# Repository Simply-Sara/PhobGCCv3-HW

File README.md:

# PhobGCCv3-HW
Seperate repository for the hardware used in the PhobGCC v3.0

The PhobGCC v3.0 board is licensed under CERN Open Hardware Licence Version 2 - Strongly Reciprocal.
This means that any changes made to the board should be made public and CHANGES.txt be updated to reflect said changes.

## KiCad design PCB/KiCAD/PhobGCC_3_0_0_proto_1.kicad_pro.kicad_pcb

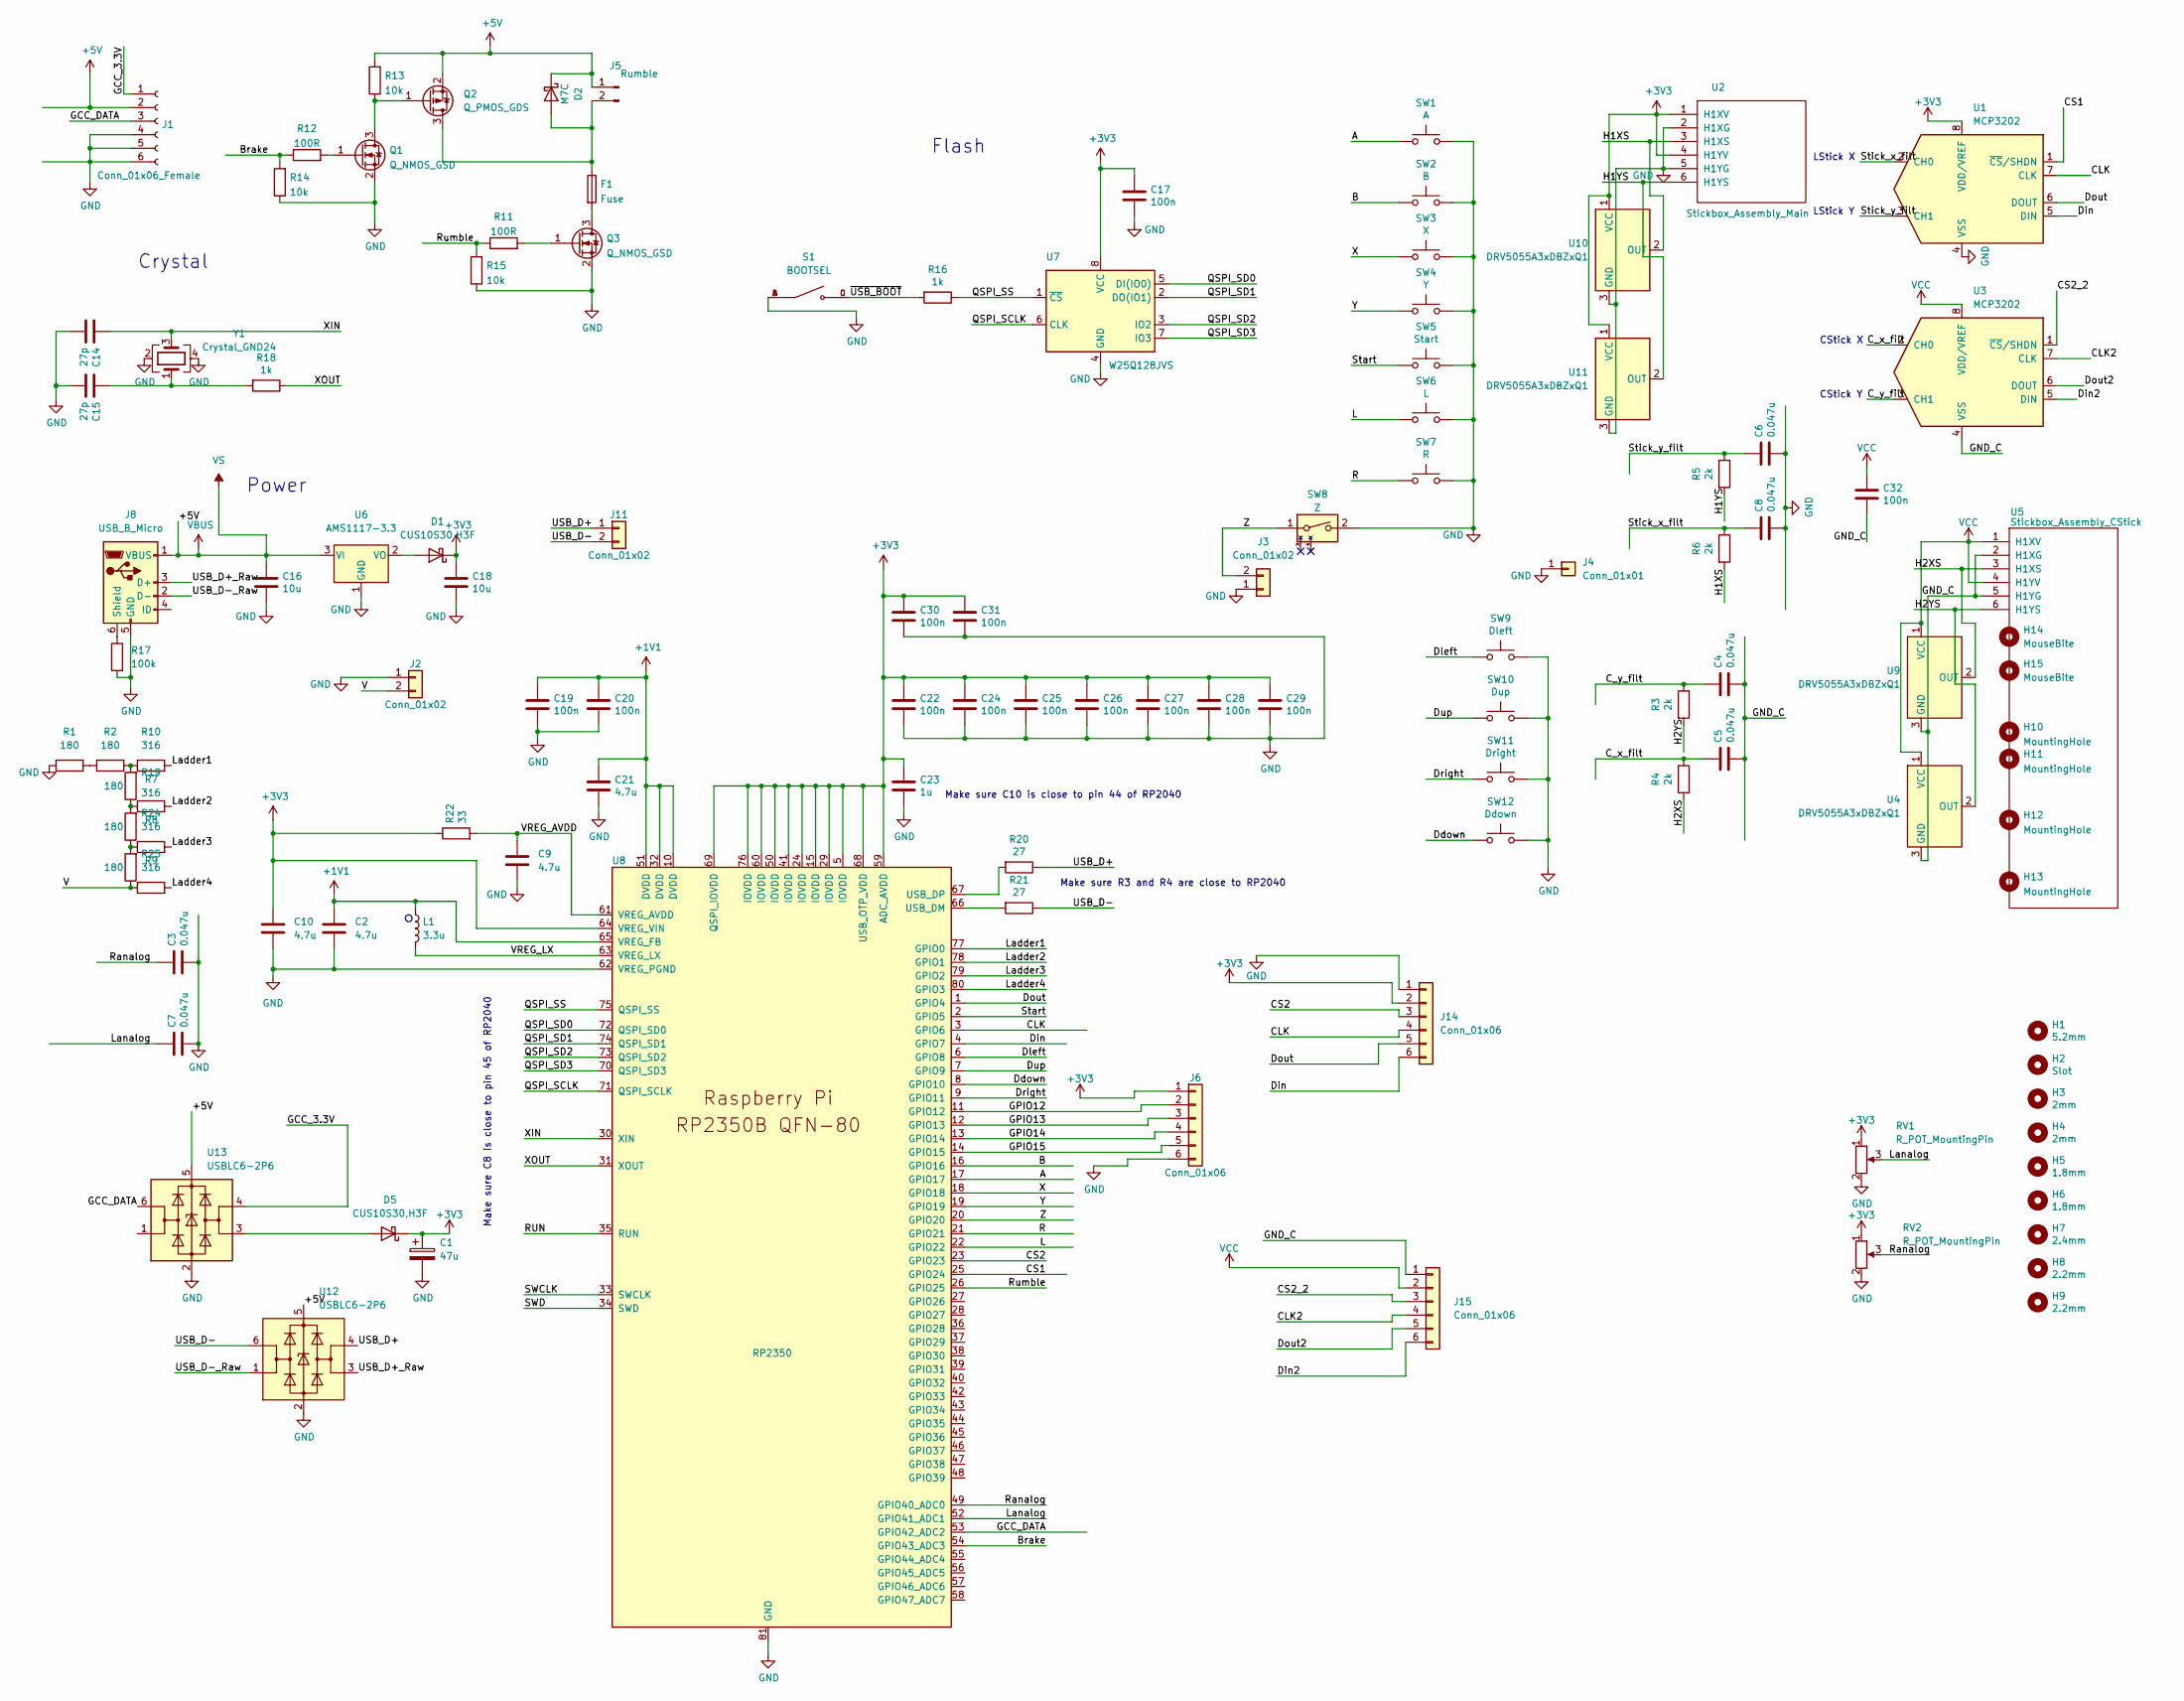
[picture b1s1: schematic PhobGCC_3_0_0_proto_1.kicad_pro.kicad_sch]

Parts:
C1: 47u; CP_EIA-3528-12_Kemet-T_Pad1.50x2.35mm_HandSolder; LCSC C136751
C2, C10: 4.7u; C_0402_1005Metric_small_pads
C3, C4, C5, C6, C7, C8: 0.047u; C_0603_HandSoldering; LCSC C1622
C9: 4.7u; C_0402_1005Metric
C14, C15: 27p; C_0402_1005Metric; LCSC C1557
C16, C18: 10u; C_0805_2012Metric; LCSC C15850
C17, C19, C20, C22, C24, C25, C26, C27, C28, C29, C30, C31, C32: 100n; C_0402_1005Metric; LCSC C1525
C21: 4.7u; C_0402_1005Metric; LCSC C52923
C23: 1u; C_0402_1005Metric; LCSC C52923
D1, D5: CUS10S30,H3F; D_SOD-323; LCSC C146335
D2: M7C; D_SOD-123; LCSC C8598
F1: Fuse; Fuse_1206_3216Metric; LCSC C69680
H1: 5.2mm; MountingHole_5.2mm
H2: Slot
H3, H4: 2mm; MountingHole_2.0mm
H5, H6: 1.8mm; MountingHole_1.8mm
H7: 2.4mm; MountingHole_2.4mm
H8, H9: 2.2mm; MountingHole_2.2mm
H10: MountingHole; MountingHole_1.8mm
H11: MountingHole; MountingHole_5.2mm
H12, H13: MountingHole; MountingHole_2.0mm
H14: MouseBite; breakaway-mousebites-double-v2-small
H15: MouseBite; breakaway-mousebites-double-v2-large
J1: Conn_01x06_Female; GCC_Header_Straight_1x06_Pitch2.00mm
J2, J11: Conn_01x02; PinHeader_1x02_P2.00mm_Vertical
J3: Conn_01x02; PinHeader_1x02_P2.00mm_Horizontal
J4: Conn_01x01; PinHeader_1x01_P2.54mm_Vertical
J5: Rumble; rumble_pins
J6, J14, J15: Conn_01x06; PinSocket_1x06_P2.00mm_Vertical
J8: USB_B_Micro; USB_Micro-B_Amphenol_10118194_Horizontal; LCSC C132563
L1: 3.3u; L_pol_2016
Q1, Q3: Q_NMOS_GSD; SOT-23; LCSC C20917
Q2: Q_PMOS_GDS; SOT-23; LCSC C15127
R1, R2, R7, R8, R9: 180; R_0402_1005Metric; LCSC C38941
R3, R4, R5, R6: 2k; R_0603_1608Metric_Pad0.98x0.95mm_HandSolder; LCSC C22975
R10, R19, R24, R25: 316; R_0402_1005Metric; LCSC C159037
R11, R12: 100R; R_0603_1608Metric_Pad0.98x0.95mm_HandSolder; LCSC C22775
R13, R14, R15: 10k; R_0603_1608Metric_Pad0.98x0.95mm_HandSolder; LCSC C25804
R16, R18: 1k; C_0402_1005Metric; LCSC C11702
R17: 100k; R_0603_1608Metric_Pad0.98x0.95mm_HandSolder; LCSC C25803
R20, R21: 27; C_0402_1005Metric; LCSC C25100
R22: 33; R_0402_1005Metric
RV1, RV2: R_POT_MountingPin; GCC_Slider
S1: BOOTSEL; SW_TS-1187A-B-A-B; PARTREV A0
SW1: A; ABXY_Contact_Omron_Switch_Circley
SW2: B; ABXY_Contact_Omron_Switch_Circley
SW3: X; ABXY_Contact_Omron_Switch_Circley
SW4: Y; ABXY_Contact_Omron_Switch_Circley
SW5: Start; Start_Contact
SW6: L; Pin_Header_Straight_1x02_Pitch2.54mm
SW7: R; Pin_Header_Straight_1x02_Pitch2.54mm
SW8: Z; Z_Switch_Edge_Omron
SW9: Dleft; Dpad_Contact_TL3315NF_2_ZigZag
SW10: Dup; Dpad_Contact_TL3315NF_2_ZigZag
SW11: Dright; Dpad_Contact_TL3315NF_2_ZigZag
SW12: Ddown; Dpad_Contact_TL3315NF_2_ZigZag
U1, U3: MCP3202; SOIC-8_3.9x4.9mm_P1.27mm; LCSC C56997
U2: Stickbox_Assembly_Main; GCC_Stickbox_Hall_Only
U4, U9, U10, U11: DRV5055A3xDBZxQ1; SOT-23; LCSC C266128
U5: Stickbox_Assembly_CStick; GCC_Stickbox_Hall_Only
U6: AMS1117-3.3; SOT-223-3_TabPin2; LCSC C6186
U7: W25Q128JVS; SOIC-8_5.23x5.23mm_P1.27mm; LCSC C97521
U8: RP2350; RP2350-QFN-80-1EP_10x10_P0.4mm_EP3.4x3.4mm_ThermalVias; LCSC C2040
U12, U13: USBLC6-2P6; SOT-666; LCSC C2827693
Y1: Crystal_GND24; Crystal_SMD_3225-4Pin_3.2x2.5mm; LCSC C40395

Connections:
+1V1: C2.1, C19.1, C20.1, C21.1, L1.1, U8.10 (DVDD), U8.32 (DVDD), U8.51 (DVDD), U8.65 (VREG_FB)
+3V3: C1.1, C10.1, C17.1, C18.1, C22.1, C23.1, C24.1, C25.1, C26.1, C27.1, C28.1, C29.1, C30.1, C31.1, D1.1 (K), D5.1 (K), J6.1, J14.2, R22.1, RV1.1 (V+), RV2.1 (V+), U1.8 (VDD/VREF), U2.1 (H1XV), U2.4 (H1YV), U7.8 (VCC), U8.5 (IOVDD), U8.15 (IOVDD), U8.24 (IOVDD), U8.29 (IOVDD), U8.41 (IOVDD), U8.50 (IOVDD), U8.59 (ADC_AVDD), U8.60 (IOVDD), U8.64 (VREG_VIN), U8.68 (USB_OTP_VDD), U8.69 (QSPI_IOVDD), U8.76 (IOVDD), U10.1 (VCC), U11.1 (VCC)
+5V: C16.1, D2.1 (K), J1.2, J5.1, J8.1 (VBUS), Q2.2 (S), R13.2, U6.3 (VI), U12.5 (VBUS), U13.5 (VBUS)
/A: SW1.1, U8.17 (GPIO17)
/B: SW2.1, U8.16 (GPIO16)
/Brake: R12.1, R14.2, U8.54 (GPIO43_ADC3)
/CLK: J14.4, U1.7 (CLK), U8.3 (GPIO6)
/CLK2: J15.4, U3.7 (CLK)
/CS1: U1.1 (~CS/SHDN), U8.25 (GPIO24)
/CS2: J14.3, U8.23 (GPIO23)
/CS2_2: J15.3, U3.1 (~CS/SHDN)
/C_x_filt: C5.1, R4.1, U3.2 (CH0)
/C_y_filt: C4.1, R3.1, U3.3 (CH1)
/Ddown: SW12.1, U8.8 (GPIO10)
/Din: J14.6, U1.5 (DIN), U8.4 (GPIO7)
/Din2: J15.6, U3.5 (DIN)
/Dleft: SW9.1, U8.6 (GPIO8)
/Dout: J14.5, U1.6 (DOUT), U8.1 (GPIO4)
/Dout2: J15.5, U3.6 (DOUT)
/Dright: SW11.1, U8.9 (GPIO11)
/Dup: SW10.1, U8.7 (GPIO9)
/GCC_3.3V: J1.1, U13.4 (I/O2)
/GCC_DATA: J1.3, U8.53 (GPIO42_ADC2), U13.6 (I/O1)
/GND_C: C4.2, C5.2, C32.2, J15.1, U3.4 (VSS), U4.3 (GND), U5.2 (H1XG), U5.5 (H1YG), U9.3 (GND)
/GPIO12: J6.2, U8.11 (GPIO12)
/GPIO13: J6.3, U8.12 (GPIO13)
/GPIO14: J6.4, U8.13 (GPIO14)
/GPIO15: J6.5, U8.14 (GPIO15)
/H1XS: R6.2, U2.3 (H1XS), U10.2 (OUT)
/H1YS: R5.2, U2.6 (H1YS), U11.2 (OUT)
/H2XS: R4.2, U5.3 (H1XS), U9.2 (OUT)
/H2YS: R3.2, U4.2 (OUT), U5.6 (H1YS)
/L: SW6.1, U8.22 (GPIO22)
/Ladder1: R10.2, U8.77 (GPIO0)
/Ladder2: R19.2, U8.78 (GPIO1)
/Ladder3: R24.2, U8.79 (GPIO2)
/Ladder4: R25.2, U8.80 (GPIO3)
/Lanalog: C7.1, RV1.3 (Signal), U8.52 (GPIO41_ADC1)
/QSPI_SCLK: U7.6 (CLK), U8.71 (QSPI_SCLK)
/QSPI_SD0: U7.5 (DI(IO0)), U8.72 (QSPI_SD0)
/QSPI_SD1: U7.2 (DO(IO1)), U8.74 (QSPI_SD1)
/QSPI_SD2: U7.3 (IO2), U8.73 (QSPI_SD2)
/QSPI_SD3: U7.7 (IO3), U8.70 (QSPI_SD3)
/QSPI_SS: R16.1, U7.1 (~CS), U8.75 (QSPI_SS)
/R: SW7.1, U8.21 (GPIO21)
/RUN: U8.35 (RUN)
/Ranalog: C3.1, RV2.3 (Signal), U8.49 (GPIO40_ADC0)
/Rumble: R11.1, R15.2, U8.26 (GPIO25)
/SWCLK: U8.33 (SWCLK)
/SWD: U8.34 (SWD)
/Start: SW5.1, U8.2 (GPIO5)
/Stick_x_filt: C8.1, R6.1, U1.2 (CH0)
/Stick_y_filt: C6.1, R5.1, U1.3 (CH1)
/USB_D+: J11.1, R20.1, U12.4 (I/O2)
/USB_D+_Raw: J8.3 (D+), U12.3 (I/O2)
/USB_D-: J11.2, R21.1, U12.6 (I/O1)
/USB_D-_Raw: J8.2 (D-), U12.1 (I/O1)
/V: J2.2, R9.1, R25.1
/VREG_AVDD: C9.1, R22.2, U8.61 (VREG_AVDD)
/VREG_LX: L1.2, U8.63 (VREG_LX)
/X: SW3.1, U8.18 (GPIO18)
/XIN: C14.1, U8.30 (XIN), Y1.3
/XOUT: R18.1, U8.31 (XOUT)
/Y: SW4.1, U8.19 (GPIO19)
/Z: J3.2, SW8.1, U8.20 (GPIO20)
/~USB_BOOT: R16.2, S1.C, S1.D
GND: C1.2, C2.2, C3.2, C6.2, C7.2, C8.2, C9.2, C10.2, C14.2, C15.2, C16.2, C17.2, C18.2, C19.2, C20.2, C21.2, C22.2, C23.2, C24.2, C25.2, C26.2, C27.2, C28.2, C29.2, C30.2, C31.2, J1.4, J1.5, J1.6, J2.1, J3.1, J4.1, J6.6, J8.5 (GND), J14.1, Q1.2 (S), Q3.2 (S), R1.2, R14.1, R15.1, R17.2, RV1.2 (GND), RV2.2 (GND), S1.A, S1.B, SW1.2, SW2.2, SW3.2, SW4.2, SW5.2, SW6.2, SW7.2, SW8.2, SW9.2, SW10.2, SW11.2, SW12.2, U1.4 (VSS), U2.2 (H1XG), U2.5 (H1YG), U6.1 (GND), U7.4 (GND), U8.62 (VREG_PGND), U8.81 (GND), U10.3 (GND), U11.3 (GND), U12.2 (GND), U13.2 (GND), Y1.2, Y1.4
unnamed: C15.1, R18.2, Y1.1
unnamed: D1.2 (A), U6.2 (VO)
unnamed: D2.2 (A), F1.1, J5.2, Q2.3 (D)
unnamed: D5.2 (A), U13.3 (I/O2)
unnamed: J8.6 (Shield), R17.1
unnamed: Q1.3 (D), Q2.1 (G), R13.1
unnamed: Q1.1 (G), R12.2
unnamed: F1.2, Q3.3 (D)
unnamed: Q3.1 (G), R11.2
unnamed: R1.1, R2.2
unnamed: R2.1, R7.2, R10.1
unnamed: R7.1, R8.2, R19.1
unnamed: R8.1, R9.2, R24.1
unnamed: R21.2, U8.66 (USB_DM)
unnamed: R20.2, U8.67 (USB_DP)
VCC: C32.1, J15.2, U3.8 (VDD/VREF), U4.1 (VCC), U5.1 (H1XV), U5.4 (H1YV), U9.1 (VCC)

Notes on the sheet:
Power
LStick Y
Make sure C10 is close to pin 44 of RP2040
CStick Y
Make sure R3 and R4 are close to RP2040
Make sure C8 is close to pin 45 of RP2040
Flash
Crystal
CStick X
LStick X

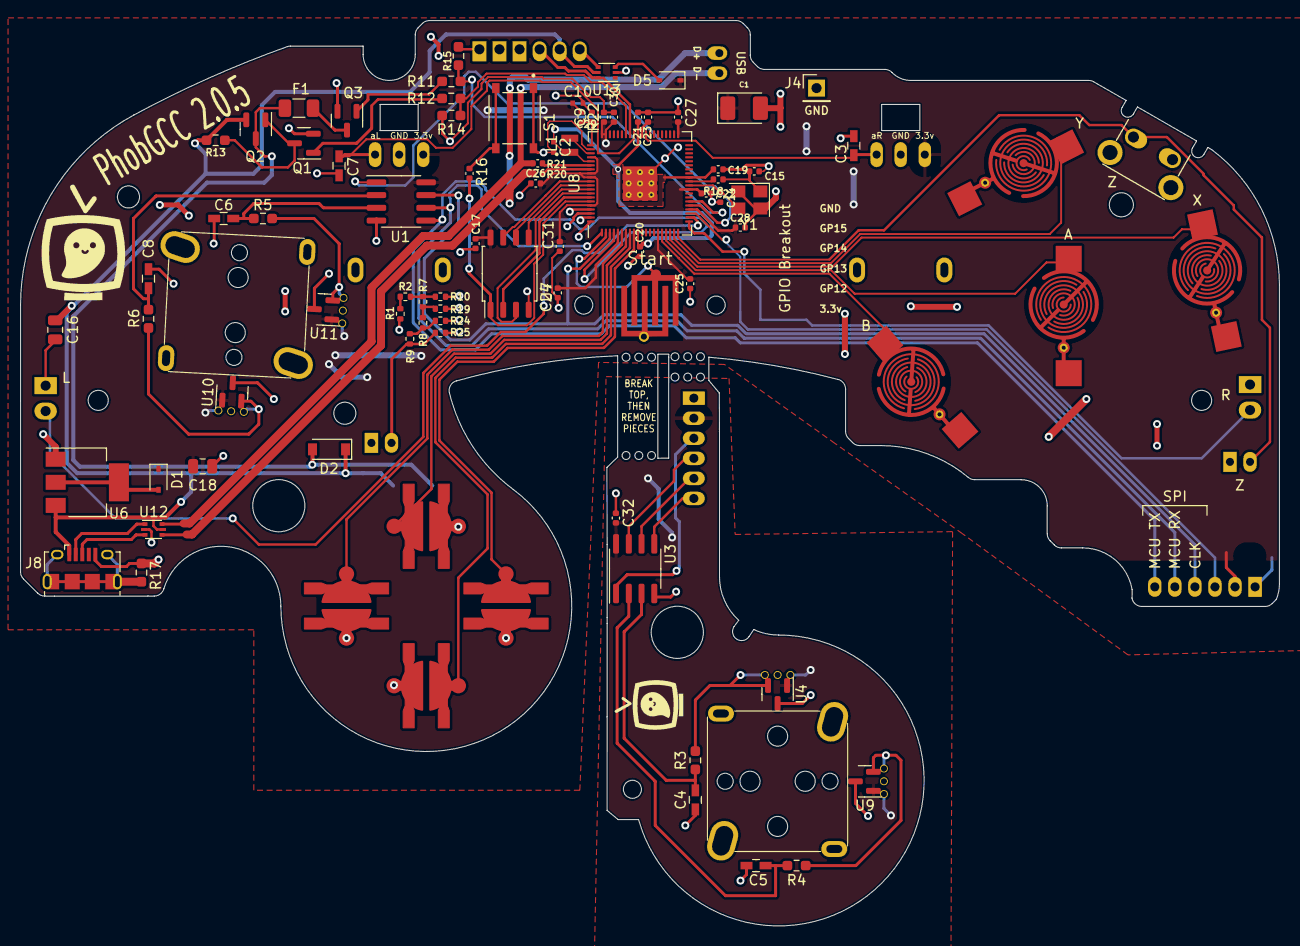
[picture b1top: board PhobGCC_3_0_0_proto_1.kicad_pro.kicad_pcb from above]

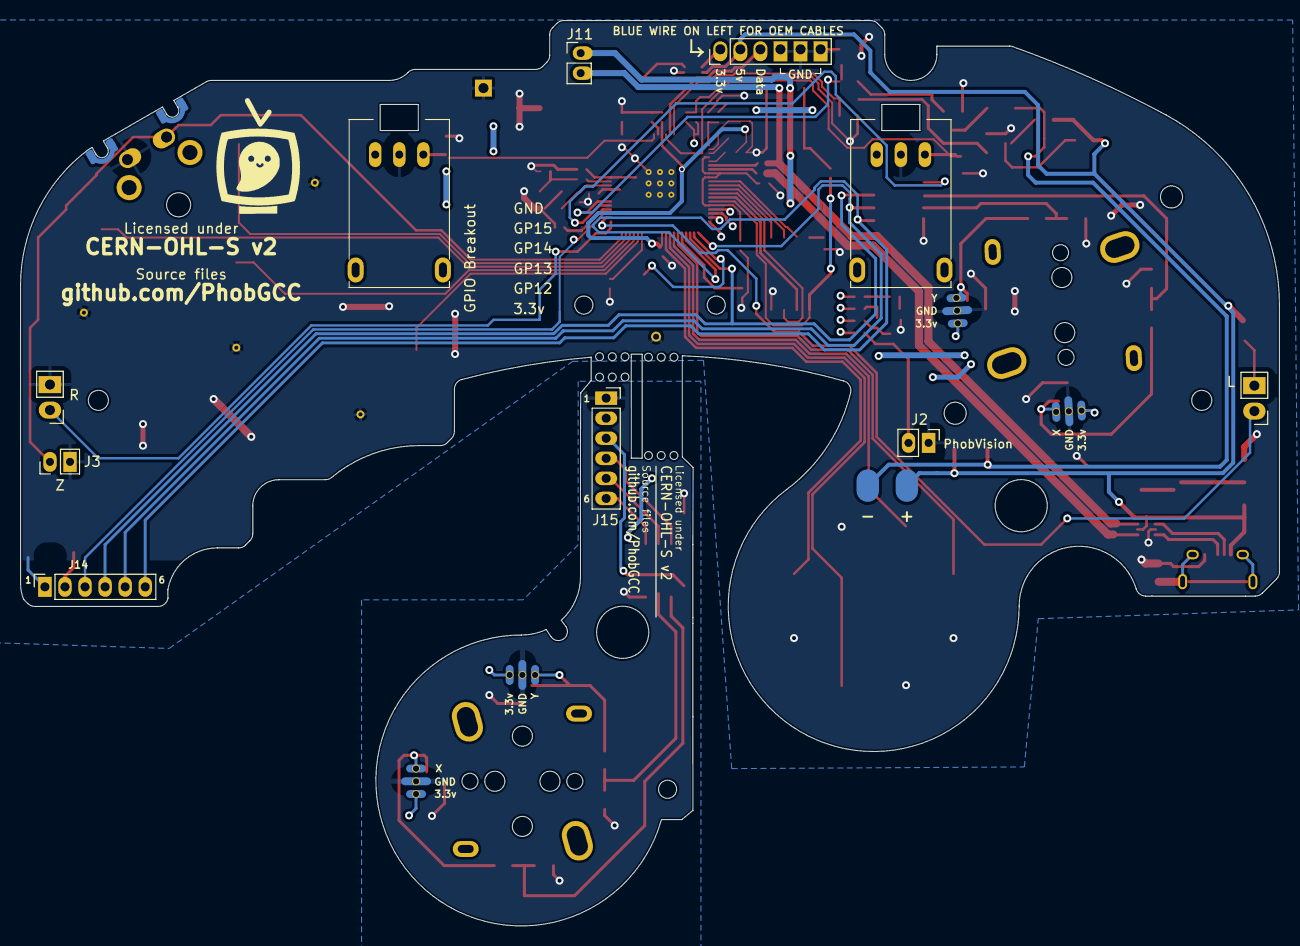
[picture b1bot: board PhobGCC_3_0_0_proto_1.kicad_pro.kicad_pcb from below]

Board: 4 copper layers, 125.5 x 90.3 mm, 117 parts (12 on the bottom side), 76 nets.

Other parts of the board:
Gphobtvbigback: LOGO; phobtv_bold_big
Gphobtvbigback#2: LOGO; phobtv_bold_big
Gtvsmallfrontc: LOGO; phobtv_bold_smol

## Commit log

2025-01-17 Updated Kicad file names to V3
2025-01-18 RP2040 to RP2350 Conversion

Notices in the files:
PCB/KiCAD/PhobGCC_3_0_0_proto_1.kicad_pro.kicad_pcb:
CERN-OHL-S v2
